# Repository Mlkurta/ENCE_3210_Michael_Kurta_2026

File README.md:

# Title of your report

## Subtitles

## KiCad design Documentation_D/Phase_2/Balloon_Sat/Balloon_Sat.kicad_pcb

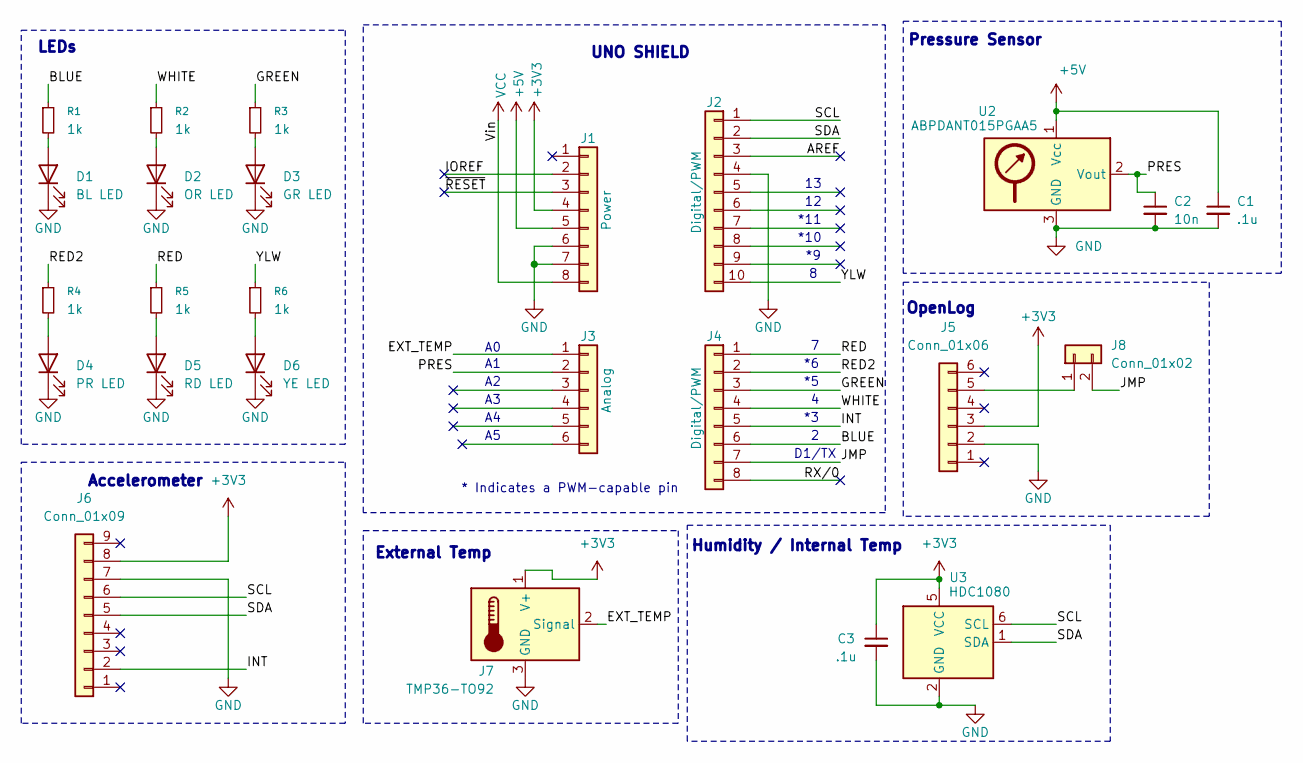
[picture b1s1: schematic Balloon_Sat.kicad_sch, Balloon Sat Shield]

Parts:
C1, C3: .1u; C_Disc_D4.3mm_W1.9mm_P5.00mm
C2: 10n; C_Disc_D4.3mm_W1.9mm_P5.00mm
D1: BL LED; LED_D5.0mm
D2: OR LED; LED_D5.0mm
D3: GR LED; LED_D5.0mm
D4: PR LED; LED_D5.0mm
D5: RD LED; LED_D5.0mm
D6: YE LED; LED_D5.0mm
J1: Power; PinSocket_1x08_P2.54mm_Vertical
J2: Digital/PWM; PinSocket_1x10_P2.54mm_Vertical
J3: Analog; PinSocket_1x06_P2.54mm_Vertical
J4: Digital/PWM; PinSocket_1x08_P2.54mm_Vertical
J5: Conn_01x06; PinSocket_1x06_P2.54mm_Vertical
J6: Conn_01x09; PinHeader_1x09_P2.54mm_Vertical
J7: TMP36-TO92; JST_PH_S3B-PH-K_1x03_P2.00mm_Horizontal
J8: Conn_01x02; PinHeader_1x02_P2.54mm_Vertical
R1, R2, R3, R4, R5, R6: 1k; R_Axial_DIN0207_L6.3mm_D2.5mm_P7.62mm_Horizontal
U2: ABPDANT015PGAA5; DIP-6_W10.45mm_LongPads
U3: HDC1080; Texas_PWSON-N6

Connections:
+3V3: C3.1, J1.4, J5.3, J6.8, J7.1 (V+), U3.5 (VCC)
+5V: C1.1, J1.5, U2.1 (Vcc)
/AREF: J2.3
/BLUE: J4.6, R1.1
/EXT_TEMP: J3.1, J7.2 (Signal)
/GREEN: J4.3, R3.1
/INT: J4.5, J6.2
/IOREF: J1.2
/JMP: J4.7, J8.2
/PRES: C2.1, J3.2, U2.2 (Vout)
/RED: J4.1, R5.1
/RED2: J4.2, R4.1
/RX/0: J4.8
/SCL: J2.1, J6.6, U3.6 (SCL)
/SDA: J2.2, J6.5, U3.1 (SDA)
/WHITE: J4.4, R2.1
/YLW: J2.10, R6.1
/~RESET: J1.3
GND: C1.2, C2.2, C3.2, D1.1 (K), D2.1 (K), D3.1 (K), D4.1 (K), D5.1 (K), D6.1 (K), J1.6, J1.7, J2.4, J5.2, J6.7, J7.3 (GND), U2.3 (GND), U3.2 (GND)
unnamed: D1.2 (A), R1.2
unnamed: D2.2 (A), R2.2
unnamed: D3.2 (A), R3.2
unnamed: D4.2 (A), R4.2
unnamed: D5.2 (A), R5.2
unnamed: D6.2 (A), R6.2
unnamed: J5.5, J8.1
VCC: J1.8

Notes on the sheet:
OpenLog
Pressure Sensor
Humidity / Internal Temp
*11
Accelerometer
D1/TX
External Temp
*10
* Indicates a PWM-capable pin
LEDs
UNO SHIELD

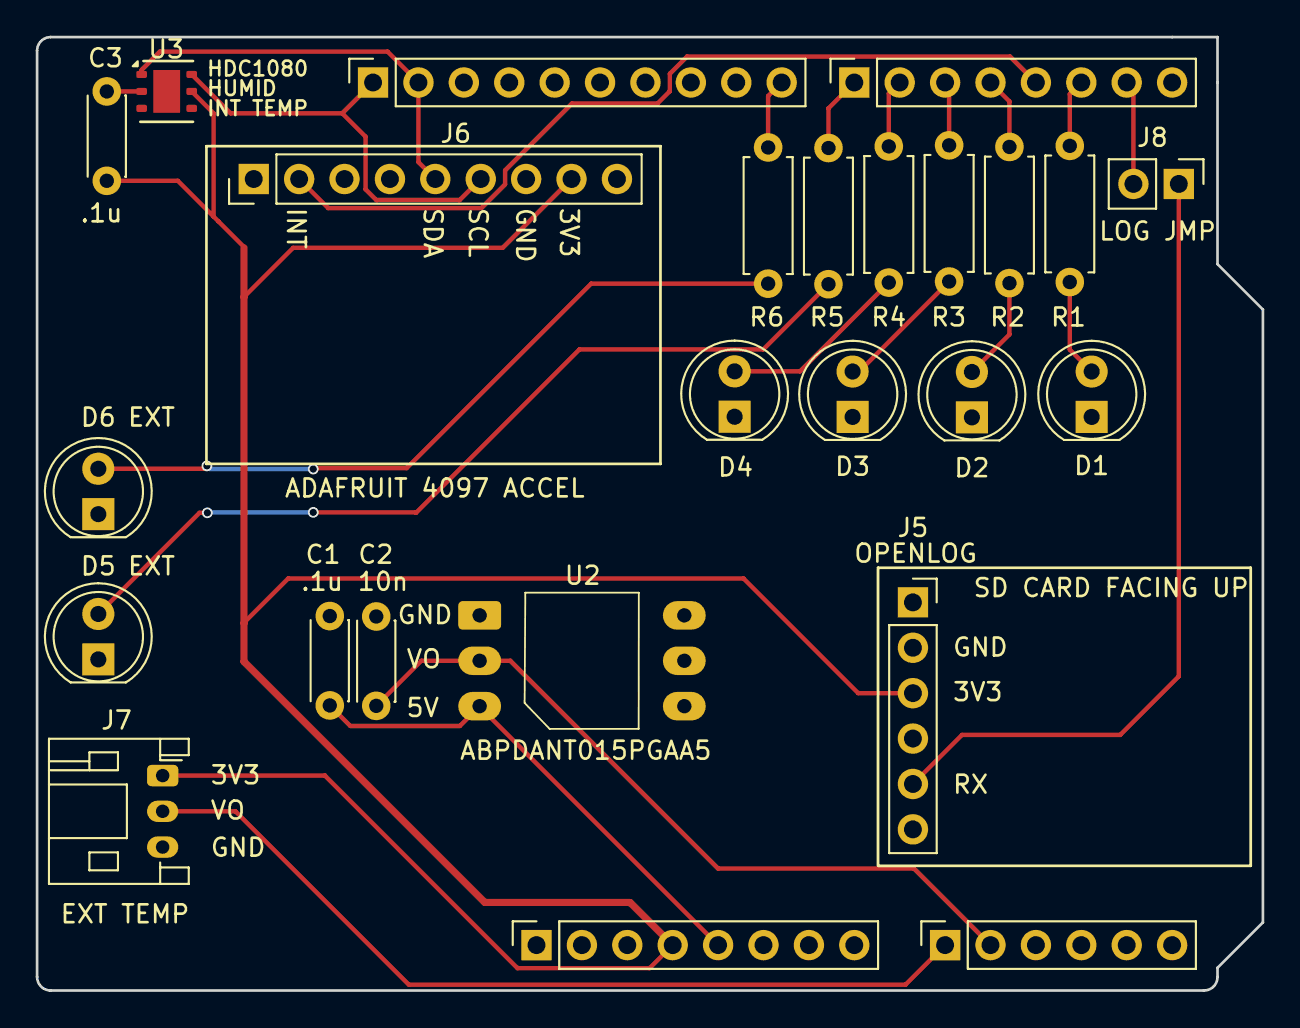
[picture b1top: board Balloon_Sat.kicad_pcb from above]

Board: 2 copper layers, 68.6 x 53.3 mm, 25 parts (0 on the bottom side), 22 nets.

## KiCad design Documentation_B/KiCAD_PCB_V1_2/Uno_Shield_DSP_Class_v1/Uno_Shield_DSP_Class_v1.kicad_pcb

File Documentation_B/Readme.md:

## Completed PCB

See KiCAD_PCB_V1_1

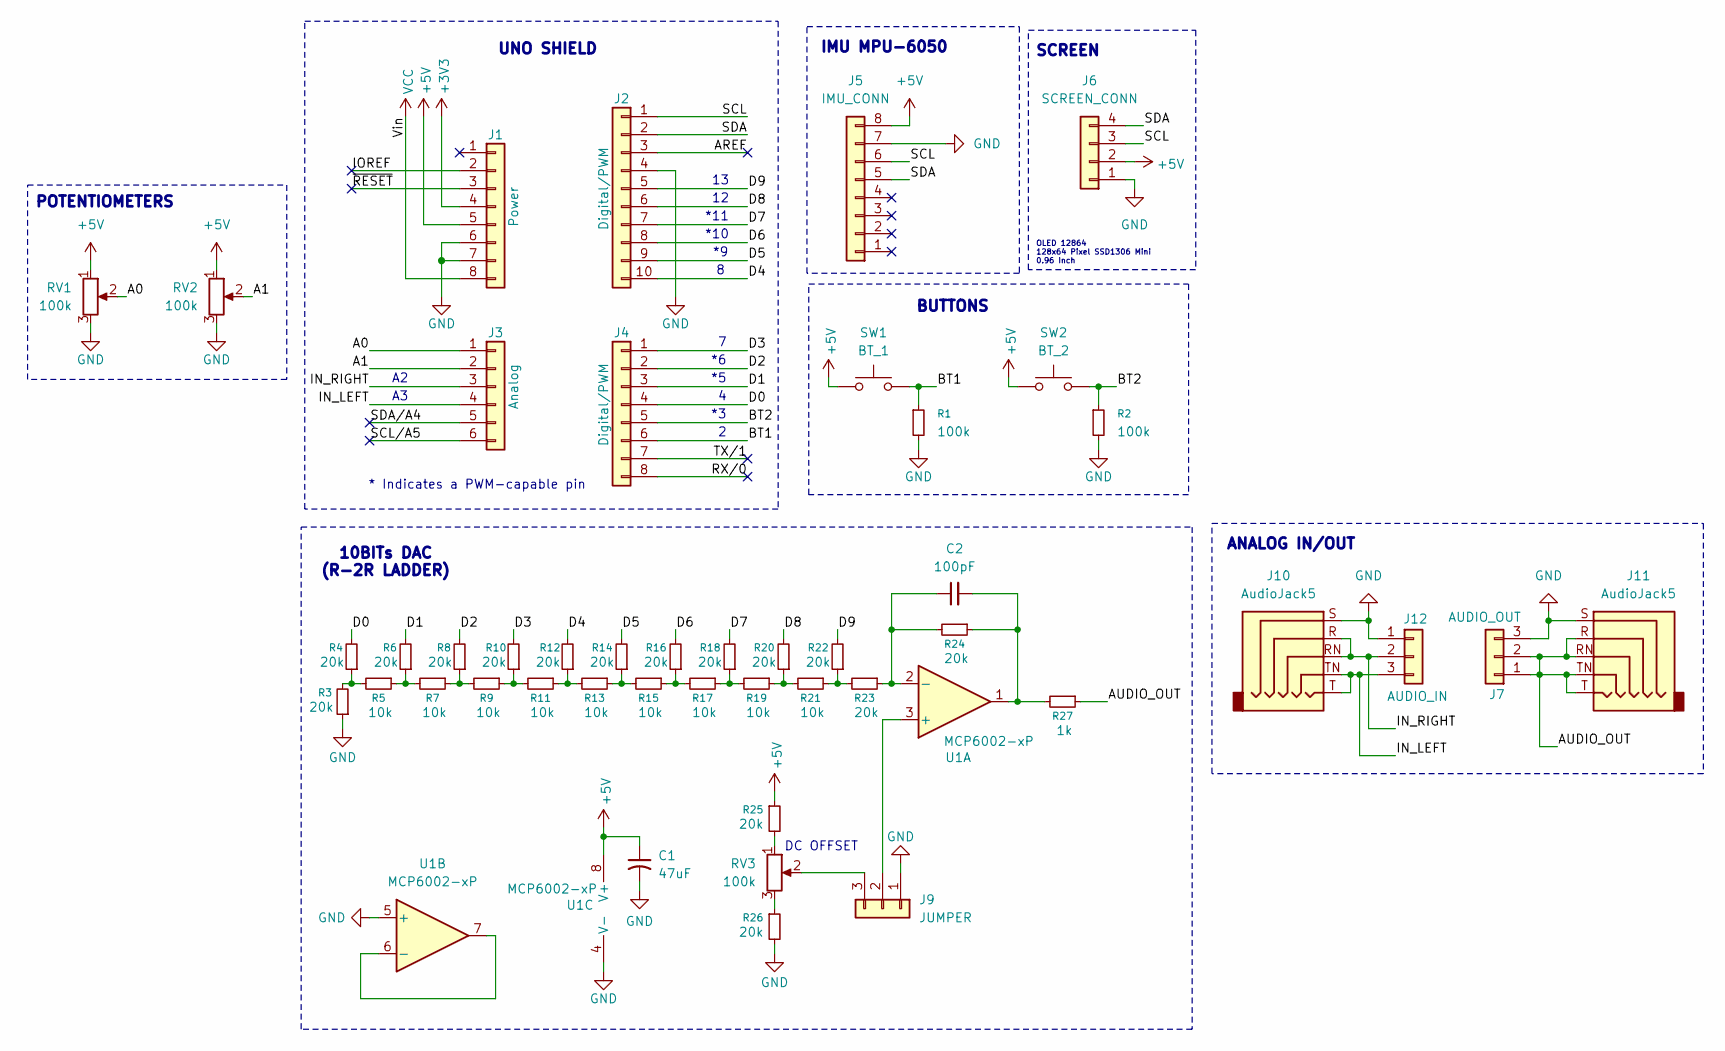
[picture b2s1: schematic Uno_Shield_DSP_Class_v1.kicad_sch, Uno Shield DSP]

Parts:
C1: 47uF; CP_Radial_D6.3mm_P2.50mm
C2: 100pF; C_Disc_D5.0mm_W2.5mm_P2.50mm
J1: Power; PinSocket_1x08_P2.54mm_Vertical
J2: Digital/PWM; PinSocket_1x10_P2.54mm_Vertical
J3: Analog; PinSocket_1x06_P2.54mm_Vertical
J4: Digital/PWM; PinSocket_1x08_P2.54mm_Vertical
J5: IMU_CONN; PinSocket_1x08_P2.54mm_Vertical
J6: SCREEN_CONN; PinHeader_1x04_P2.54mm_Vertical
J7: AUDIO_OUT; PinHeader_1x03_P2.54mm_Vertical
J9: JUMPER; PinHeader_1x03_P2.54mm_Vertical
J10, J11: AudioJack5; Jack_3.5mm_CUI_SJ1-3525N_Horizontal
J12: AUDIO_IN; PinHeader_1x03_P2.54mm_Vertical
R1, R2: 100k; R_Axial_DIN0309_L9.0mm_D3.2mm_P2.54mm_Vertical
R3, R4, R6, R8, R10, R12, R14, R16, R18, R20, R22, R23, R24, R25, R26: 20k; R_Axial_DIN0309_L9.0mm_D3.2mm_P2.54mm_Vertical
R5, R7, R9, R11, R13, R15, R17, R19, R21: 10k; R_Axial_DIN0309_L9.0mm_D3.2mm_P2.54mm_Vertical
R27: 1k; R_Axial_DIN0309_L9.0mm_D3.2mm_P2.54mm_Vertical
RV1, RV2, RV3: 100k; Potentiometer_Bourns_3386P_Vertical
SW1: BT_1; SW_PUSH_6mm
SW2: BT_2; SW_PUSH_6mm
U1: MCP6002-xP; DIP-8_W7.62mm_Socket_LongPads

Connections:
+3V3: J1.4
+5V: C1.1, J1.5, J5.8, J6.2, R25.1, RV1.1, RV2.1, SW1.1, SW2.1, U1.8 (V+)
/A0: J3.1, RV1.2
/A1: J3.2, RV2.2
/AREF: J2.3
/AUDIO_OUT: J7.1, J7.2, J11.R, J11.RN, J11.T, J11.TN, R27.1
/BT1: J4.6, R1.1, SW1.2
/BT2: J4.5, R2.1, SW2.2
/D0: J4.4, R4.2
/D1: J4.3, R6.2
/D2: J4.2, R8.2
/D3: J4.1, R10.2
/D4: J2.10, R12.2
/D5: J2.9, R14.2
/D6: J2.8, R16.2
/D7: J2.7, R18.2
/D8: J2.6, R20.2
/D9: J2.5, R22.2
/IN_LEFT: J3.4, J10.T, J10.TN, J12.3
/IN_RIGHT: J3.3, J10.R, J10.RN, J12.2
/IOREF: J1.2
/RX/0: J4.8
/SCL: J2.1, J5.6, J6.3
/SCL/A5: J3.6
/SDA: J2.2, J5.5, J6.4
/SDA/A4: J3.5
/TX/1: J4.7
/~RESET: J1.3
GND: C1.2, J1.6, J1.7, J2.4, J5.7, J6.1, J7.3, J9.1, J10.S, J11.S, J12.1, R1.2, R2.2, R3.1, R26.2, RV1.3, RV2.3, U1.4 (V-), U1.5 (+)
unnamed: C2.2, R24.1, R27.2, U1.1
unnamed: J9.2, U1.3 (+)
unnamed: J9.3, RV3.2
unnamed: R3.2, R4.1, R5.2
unnamed: R5.1, R6.1, R7.2
unnamed: R7.1, R8.1, R9.2
unnamed: R9.1, R10.1, R11.2
unnamed: R11.1, R12.1, R13.2
unnamed: R13.1, R14.1, R15.2
unnamed: R15.1, R16.1, R17.2
unnamed: R17.1, R18.1, R19.2
unnamed: R19.1, R20.1, R21.2
unnamed: R21.1, R22.1, R23.2
unnamed: R25.2, RV3.1
unnamed: R26.1, RV3.3
unnamed: C2.1, R23.1, R24.2, U1.2 (-)
unnamed: U1.6 (-), U1.7
VCC: J1.8

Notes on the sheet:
BUTTONS
IMU MPU-6050
POTENTIOMETERS
*11
DC OFFSET
10BITs DAC (R-2R LADDER)
ANALOG IN/OUT
*10
OLED 12864 128x64 Pixel SSD1306 Mini 0.96 Inch
* Indicates a PWM-capable pin
SCREEN
UNO SHIELD

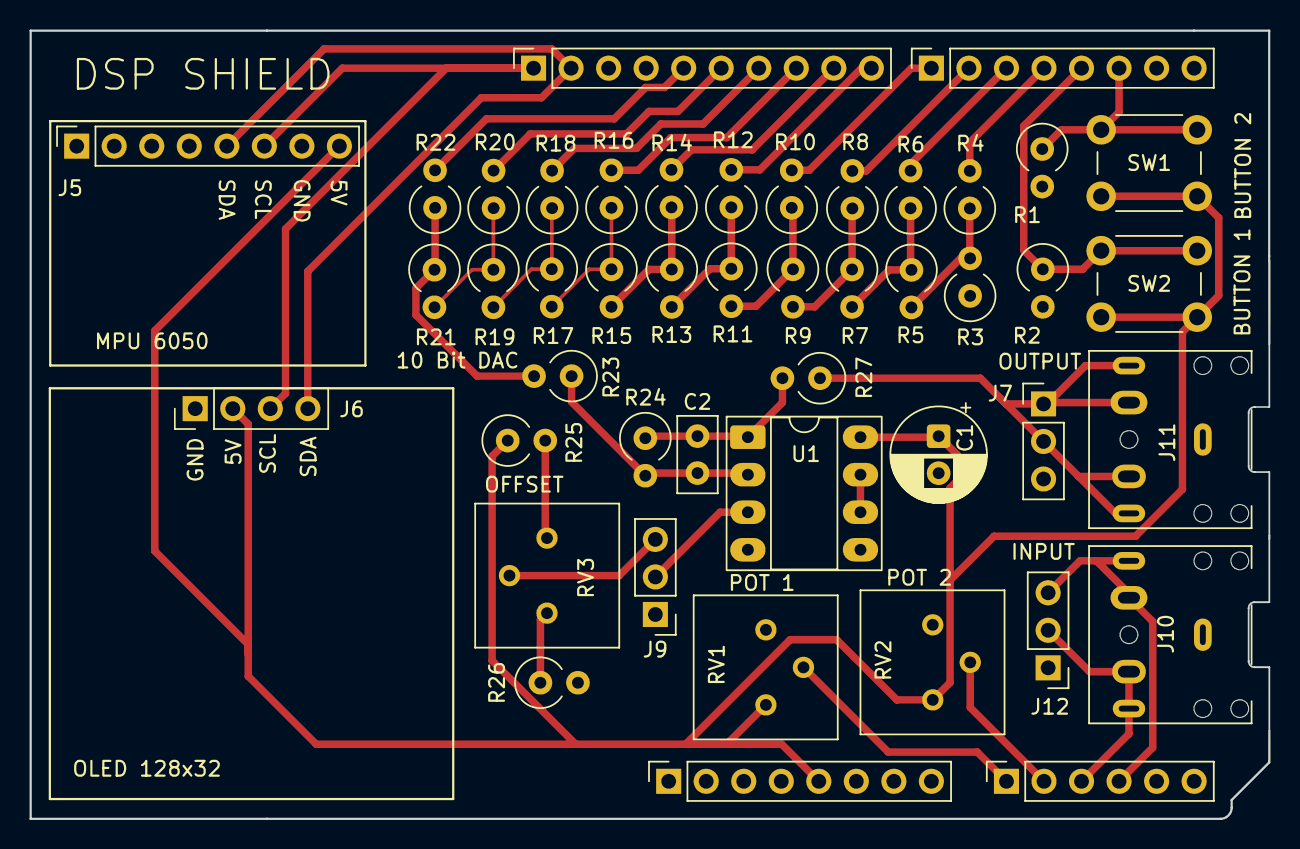
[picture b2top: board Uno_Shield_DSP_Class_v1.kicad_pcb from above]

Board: 2 copper layers, 83.8 x 53.3 mm, 46 parts (0 on the bottom side), 38 nets.

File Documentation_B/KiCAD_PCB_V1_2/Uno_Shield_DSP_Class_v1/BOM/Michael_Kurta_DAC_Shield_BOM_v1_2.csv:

"Id";"Designator";"Footprint";"Quantity";"Designation";"Supplier and ref";
1;"J1";"PinSocket_1x08_P2.54mm_Vertical";1;"Power";;;
2;"J3";"PinSocket_1x06_P2.54mm_Vertical";1;"Analog";;;
3;"J2";"PinSocket_1x10_P2.54mm_Vertical";1;"Digital/PWM";;;
4;"J4";"PinSocket_1x08_P2.54mm_Vertical";1;"Digital/PWM";;;
5;"R9,R13,R15,R19,R7,R21,R5,R11,R17";"R_Axial_DIN0309_L9.0mm_D3.2mm_P2.54mm_Vertical";9;"10k";;;
6;"R14,R18,R4,R20,R6,R10,R26,R24,R12,R22,R25,R16,R3,R8,R23";"R_Axial_DIN0309_L9.0mm_D3.2mm_P2.54mm_Vertical";15;"20k";;;
7;"C2";"C_Disc_D5.0mm_W2.5mm_P2.50mm";1;"100pF";;;
8;"SW2";"SW_PUSH_6mm";1;"BT_2";;;
9;"J7";"PinHeader_1x03_P2.54mm_Vertical";1;"AUDIO_OUT";;;
10;"J5";"PinSocket_1x08_P2.54mm_Vertical";1;"IMU_CONN";;;
11;"J11,J10";"Jack_3.5mm_CUI_SJ1-3525N_Horizontal";2;"AudioJack5";;;
12;"C1";"CP_Radial_D6.3mm_P2.50mm";1;"47uF";;;
13;"SW1";"SW_PUSH_6mm";1;"BT_1";;;
14;"J12";"PinHeader_1x03_P2.54mm_Vertical";1;"AUDIO_IN";;;
15;"R1,R2";"R_Axial_DIN0309_L9.0mm_D3.2mm_P2.54mm_Vertical";2;"100k";;;
16;"R27";"R_Axial_DIN0309_L9.0mm_D3.2mm_P2.54mm_Vertical";1;"1k";;;
17;"RV1,RV3,RV2";"Potentiometer_Bourns_3386P_Vertical";3;"100k";;;
18;"U1";"DIP-8_W7.62mm_Socket_LongPads";1;"MCP6002-xP";;;
19;"J9";"PinHeader_1x03_P2.54mm_Vertical";1;"JUMPER";;;
20;"J6";"PinHeader_1x04_P2.54mm_Vertical";1;"SCREEN_CONN";;;

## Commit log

2026-01-09 my test file
2026-01-09 Add initial structure to README.md
2026-01-11 Enhance color detection with LED control
    Added pin definitions and LED control for color detection.
2026-01-11 Enhance comments and structure in quadratic.c
    Added comments for better understanding and clarity.
2026-01-11 Refactor second_max.c with comments and formatting
    Added comments for clarity and improved code readability.
2026-01-11 Added cosine printer.
2026-01-12 Update readme with exercise descriptions
    Added descriptions for quadratic and user_entered_array programs.
2026-01-12 Update readme to include sum and average details
    Added functionality to print the sum and average of user-entered integers.
2026-01-12 Update readme with image and fix typo
    Added an image to the readme and corrected a typo in the user_entered_array description.
2026-01-12 Add R_G_B_string.ino problem description
    Added a new section for the R_G_B_string.ino problem, detailing the task and expected outcomes.
2026-01-12 Update readme with pattern detection program details
    Added description for pattern detection program and its functionality.
2026-01-14 Update readme with simple_calculator.ino details
    Added description for simple_calculator.ino functionality.
2026-01-14 Update readme with project details and images
    Added images and clarified project descriptions for LED sequence and simple calculator.
2026-01-16 Remove image tag from Lab1 readme
    Removed an image tag from the readme file.
2026-01-16 Enhance readme with image and memory details
    Updated the readme to include an image and clarify memory requirements for the program.
2026-02-27 Create Part4
2026-02-27 Add GIF to Readme.md
2026-03-02 Add introduction section to Readme.md
2026-03-03 Enhance Readme with DAC project details
    Added detailed descriptions of the design, prototyping, and PCB design stages for the DAC project, including images and explanations of components used.
2026-03-04 Change image links to HTML format in Readme.md
    Updated image syntax in Readme.md to use HTML tags.
2026-03-09 Add additional components and block diagram to README
2026-03-13 Add block diagram image to README
